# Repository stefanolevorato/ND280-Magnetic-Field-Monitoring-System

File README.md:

# I2C-TMAG Sensor Array

Project for ATmega328PB-based TMAG5273 magnetic sensor bring-up and future sensor array development.

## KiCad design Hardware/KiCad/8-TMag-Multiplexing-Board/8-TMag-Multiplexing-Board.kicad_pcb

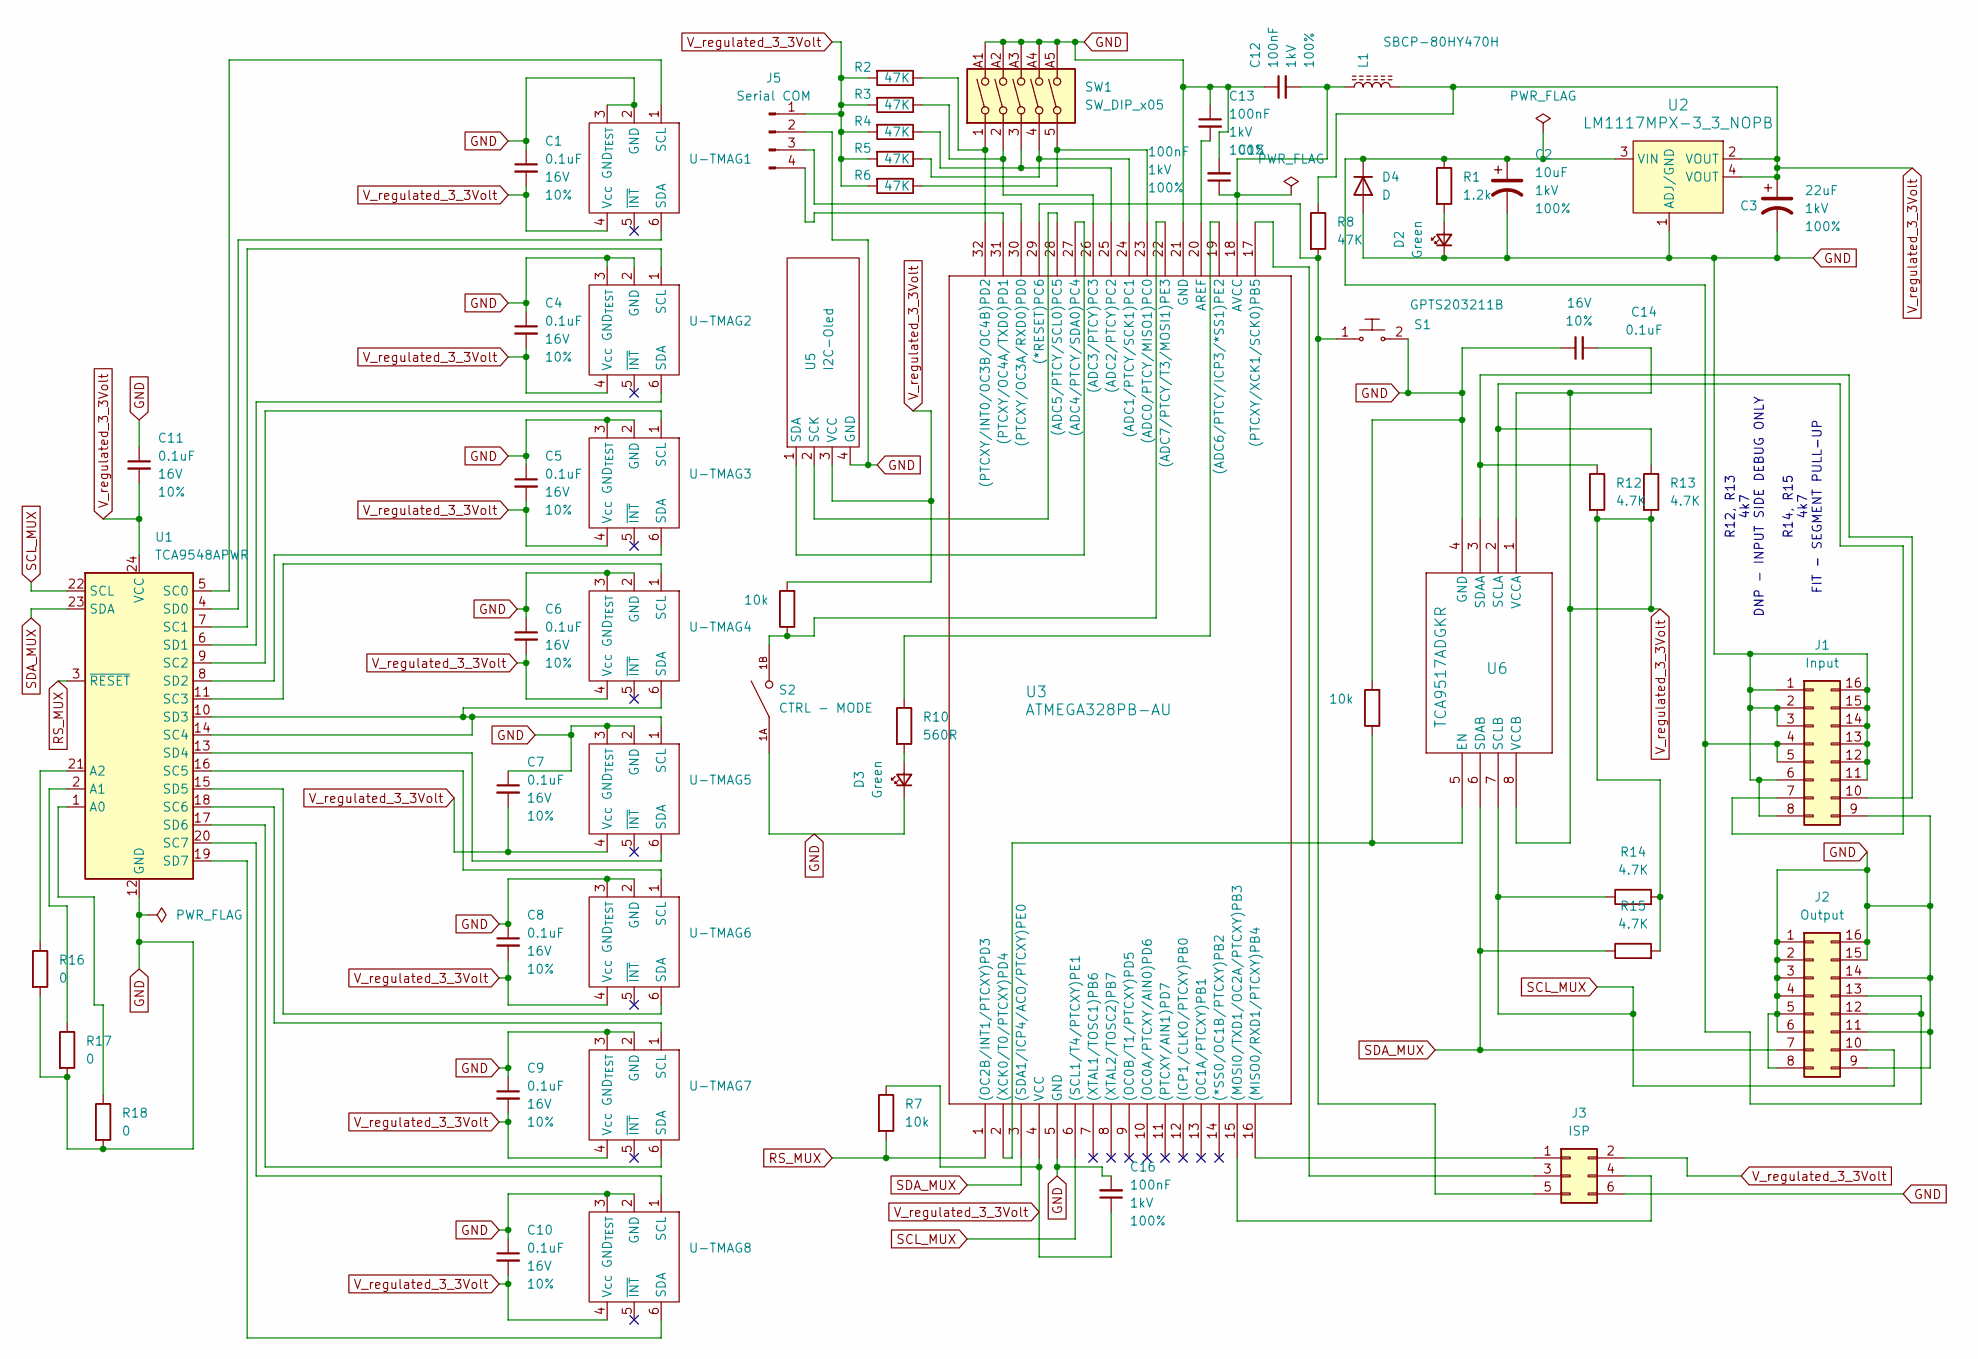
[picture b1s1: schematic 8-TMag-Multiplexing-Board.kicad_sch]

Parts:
C1, C4, C5, C6, C7, C8, C9, C10, C11, C14: 0.1uF; C_0402_1005Metric; Voltage 16V; Tolerance 10%
C2: 10uF; CP_Radial_D4.0mm_P2.00mm; Voltage 1kV; Tolerance 100%
C3: 22uF; CP_Radial_D4.0mm_P2.00mm; Voltage 1kV; Tolerance 100%
C12, C13, C15, C16: 100nF; C_0603_1608Metric; Voltage 1kV; Tolerance 100%
D2, D3: Green; LED_1206_Bottom_Green
D4: D; D_1206_3216Metric_Pad1.42x1.75mm_HandSolder
J1: Input; PinSocket_2x08_P2.54mm_Horizontal
J2: Output; PinSocket_2x08_P2.54mm_Horizontal
J3: ISP; PinHeader_2x03_P2.54mm_Vertical
J5: Serial COM; 1x04_P2.54mm
L1: SBCP-80HY470H; CP_Radial_D5.0mm_P2.50mm
R1: 1.2k; R_1206_3216Metric_Pad1.30x1.75mm_HandSolder
R2, R3, R4, R5, R6, R8: 47K; R_1206_3216Metric_Pad1.30x1.75mm_HandSolder
R7, R9, R11: 10k; R_1206_3216Metric_Pad1.30x1.75mm_HandSolder
R10: 560R; R_1206_3216Metric_Pad1.30x1.75mm_HandSolder
R12, R13, R14, R15: 4.7K; R_1206_3216Metric_Pad1.30x1.75mm_HandSolder
R16, R17, R18: 0; R_1206_3216Metric_Pad1.30x1.75mm_HandSolder
S1: GPTS203211B; PushButton_12x12mm_THT_GPTS203211B; MPN GPTS203211B; Digi-Key_PN CW181-ND
S2: CTRL - MODE; SW_DS01-254-L-01BE; PARTREV 1.0
SW1: SW_DIP_x05; 416131160805
U1: TCA9548APWR; TSSOP-24_4.4x7.8mm_P0.65mm
U2: LM1117MPX-3_3_NOPB; SOT-223; MPN LM1117MPX-3.3/NOPB; Digi-Key_PN LM1117MPX-3.3/NOPBCT-ND
U3: ATMEGA328PB-AU; 32A_MCH-M
U5: I2C-Oled; Oled128-32I2C
U6: TCA9517ADGKR; DGK8_TEX-L
U-TMAG1, U-TMAG2, U-TMAG3, U-TMAG4, U-TMAG5, U-TMAG6, U-TMAG7, U-TMAG8: TMAG5723-SOT23-I2C

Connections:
GND: C1.1, C2.2, C3.2, C4.1, C5.1, C6.1, C7.1, C8.1, C9.1, C10.1, C11.1, C12.1, C13.1, C14.1, C15.2, C16.2, D2.1 (K), D3.1 (K), D4.2 (A), J1.1, J1.2, J1.3, J1.6, J1.8, J1.9, J1.11, J1.12, J1.13, J1.14, J1.15, J1.16, J2.1, J2.2, J2.3, J2.4, J2.5, J2.6, J2.8, J2.9, J2.11, J2.14, J2.15, J2.16, J3.6, J5.2, R11.2, R16.2, R17.2, R18.2, S1.2, S2.1A, SW1.A1, SW1.A2, SW1.A3, SW1.A4, SW1.A5, U1.12 (GND), U2.1 (ADJ/GND), U3.5 (GND), U3.21 (GND), U5.4 (GND), U6.4 (GND), U-TMAG1.2 (GND), U-TMAG1.3 (GND_{TEST}), U-TMAG2.2 (GND), U-TMAG2.3 (GND_{TEST}), U-TMAG3.2 (GND), U-TMAG3.3 (GND_{TEST}), U-TMAG4.2 (GND), U-TMAG4.3 (GND_{TEST}), U-TMAG5.2 (GND), U-TMAG5.3 (GND_{TEST}), U-TMAG6.2 (GND), U-TMAG6.3 (GND_{TEST}), U-TMAG7.2 (GND), U-TMAG7.3 (GND_{TEST}), U-TMAG8.2 (GND), U-TMAG8.3 (GND_{TEST})
unnamed: D2.2 (A), R1.2
unnamed: D3.2 (A), R10.2
unnamed: C2.1, D4.1 (K), J1.4, J1.5, J2.12, J2.13, R1.1, U2.3 (VIN)
unnamed: J1.7, R13.1, U6.2 (SCLA)
unnamed: J1.10, R12.1, U6.3 (SDAA)
unnamed: J3.1, U3.16 ((MISO0/RXD1/PTCXY)PB4)
unnamed: J3.3, U3.17 ((PTCXY/XCK1/SCK0)PB5)
unnamed: J3.4, U3.15 ((MOSI0/TXD1/OC2A/PTCXY)PB3)
unnamed: J3.5, R8.2, S1.1, U3.29 ((*RESET)PC6)
unnamed: J5.3, U3.30 ((PTCXY/OC3A/RXD0)PD0)
unnamed: J5.4, U3.31 ((PTCXY/OC4A/TXD0)PD1)
unnamed: R18.1, U1.1 (A0)
unnamed: R17.1, U1.2 (A1)
unnamed: R16.1, U1.21 (A2)
unnamed: R6.1, SW1.5, U3.23 ((ADC0/PTCY/MISO1)PC0)
unnamed: R5.1, SW1.4, U3.24 ((ADC1/PTCY/SCK1)PC1)
unnamed: R4.1, SW1.3, U3.25 ((ADC2/PTCY)PC2)
unnamed: R3.1, SW1.2, U3.26 ((ADC3/PTCY)PC3)
unnamed: U3.27 ((ADC4/PTCY/SDA0)PC4), U5.1 (SDA)
unnamed: U3.28 ((ADC5/PTCY/SCL0)PC5), U5.2 (SCK)
unnamed: R10.1, U3.19 ((ADC6/PTCY/ICP3/*SS1)PE2)
unnamed: R9.1, S2.1B, U3.22 ((ADC7/PTCY/T3/MOSI1)PE3)
unnamed: R2.1, SW1.1, U3.32 ((PTCXY/INT0/OC3B/OC4B)PD2)
unnamed: R11.1, U3.2 ((XCK0/T0/PTCXY)PD4), U6.5 (EN)
unnamed: C13.2, U3.20 (AREF)
unnamed: C12.2, C15.1, L1.1, U3.18 (AVCC)
unnamed: U1.5 (SC0), U-TMAG1.1 (SCL)
unnamed: U1.4 (SD0), U-TMAG1.6 (SDA)
unnamed: U1.7 (SC1), U-TMAG2.1 (SCL)
unnamed: U1.6 (SD1), U-TMAG2.6 (SDA)
unnamed: U1.9 (SC2), U-TMAG3.1 (SCL)
unnamed: U1.8 (SD2), U-TMAG3.6 (SDA)
unnamed: U1.11 (SC3), U-TMAG4.1 (SCL)
unnamed: U1.10 (SD3), U1.14 (SC4), U-TMAG4.6 (SDA), U-TMAG5.1 (SCL)
unnamed: U1.13 (SD4), U-TMAG5.6 (SDA)
unnamed: U1.16 (SC5), U-TMAG6.1 (SCL)
unnamed: U1.15 (SD5), U-TMAG6.6 (SDA)
unnamed: U1.18 (SC6), U-TMAG7.1 (SCL)
unnamed: U1.17 (SD6), U-TMAG7.6 (SDA)
unnamed: U1.20 (SC7), U-TMAG8.1 (SCL)
unnamed: U1.19 (SD7), U-TMAG8.6 (SDA)
RS_MUX: R7.2, U1.3 (~RESET), U3.1 ((OC2B/INT1/PTCXY)PD3)
SCL_MUX: J2.10, R14.1, U1.22 (SCL), U3.6 ((SCL1/T4/PTCXY)PE1), U6.7 (SCLB)
SDA_MUX: J2.7, R15.1, U1.23 (SDA), U3.3 ((SDA1/ICP4/ACO/PTCXY)PE0), U6.6 (SDAB)
V_regulated_3_3Volt: C1.2, C3.1, C4.2, C5.2, C6.2, C7.2, C8.2, C9.2, C10.2, C11.2, C14.2, C16.1, J3.2, J5.1, L1.2, R2.2, R3.2, R4.2, R5.2, R6.2, R7.1, R8.1, R9.2, R12.2, R13.2, R14.2, R15.2, U1.24 (VCC), U2.2 (VOUT), U2.4 (VOUT), U3.4 (VCC), U5.3 (VCC), U6.1 (VCCA), U6.8 (VCCB), U-TMAG1.4 (Vcc), U-TMAG2.4 (Vcc), U-TMAG3.4 (Vcc), U-TMAG4.4 (Vcc), U-TMAG5.4 (Vcc), U-TMAG6.4 (Vcc), U-TMAG7.4 (Vcc), U-TMAG8.4 (Vcc)

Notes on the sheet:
R12, R13 4k7 DNP - INPUT SIDE DEBUG ONLY R14, R15 4k7 FIT - SEGMENT PULL-UP

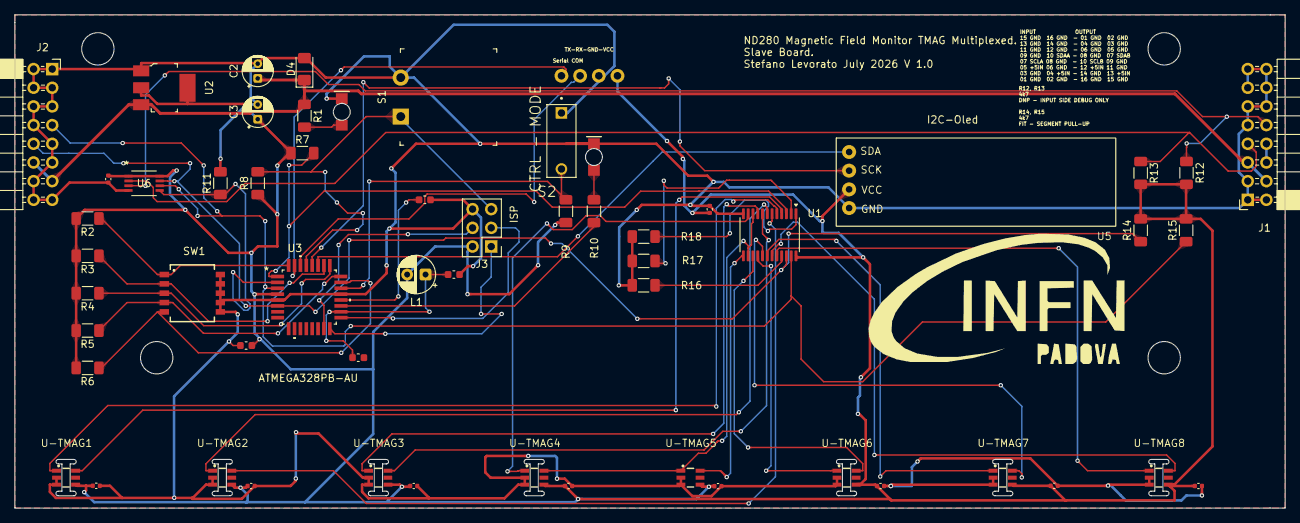
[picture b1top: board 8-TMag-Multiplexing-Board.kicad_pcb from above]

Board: 2 copper layers, 172.7 x 67.1 mm, 58 parts (0 on the bottom side), 46 nets.

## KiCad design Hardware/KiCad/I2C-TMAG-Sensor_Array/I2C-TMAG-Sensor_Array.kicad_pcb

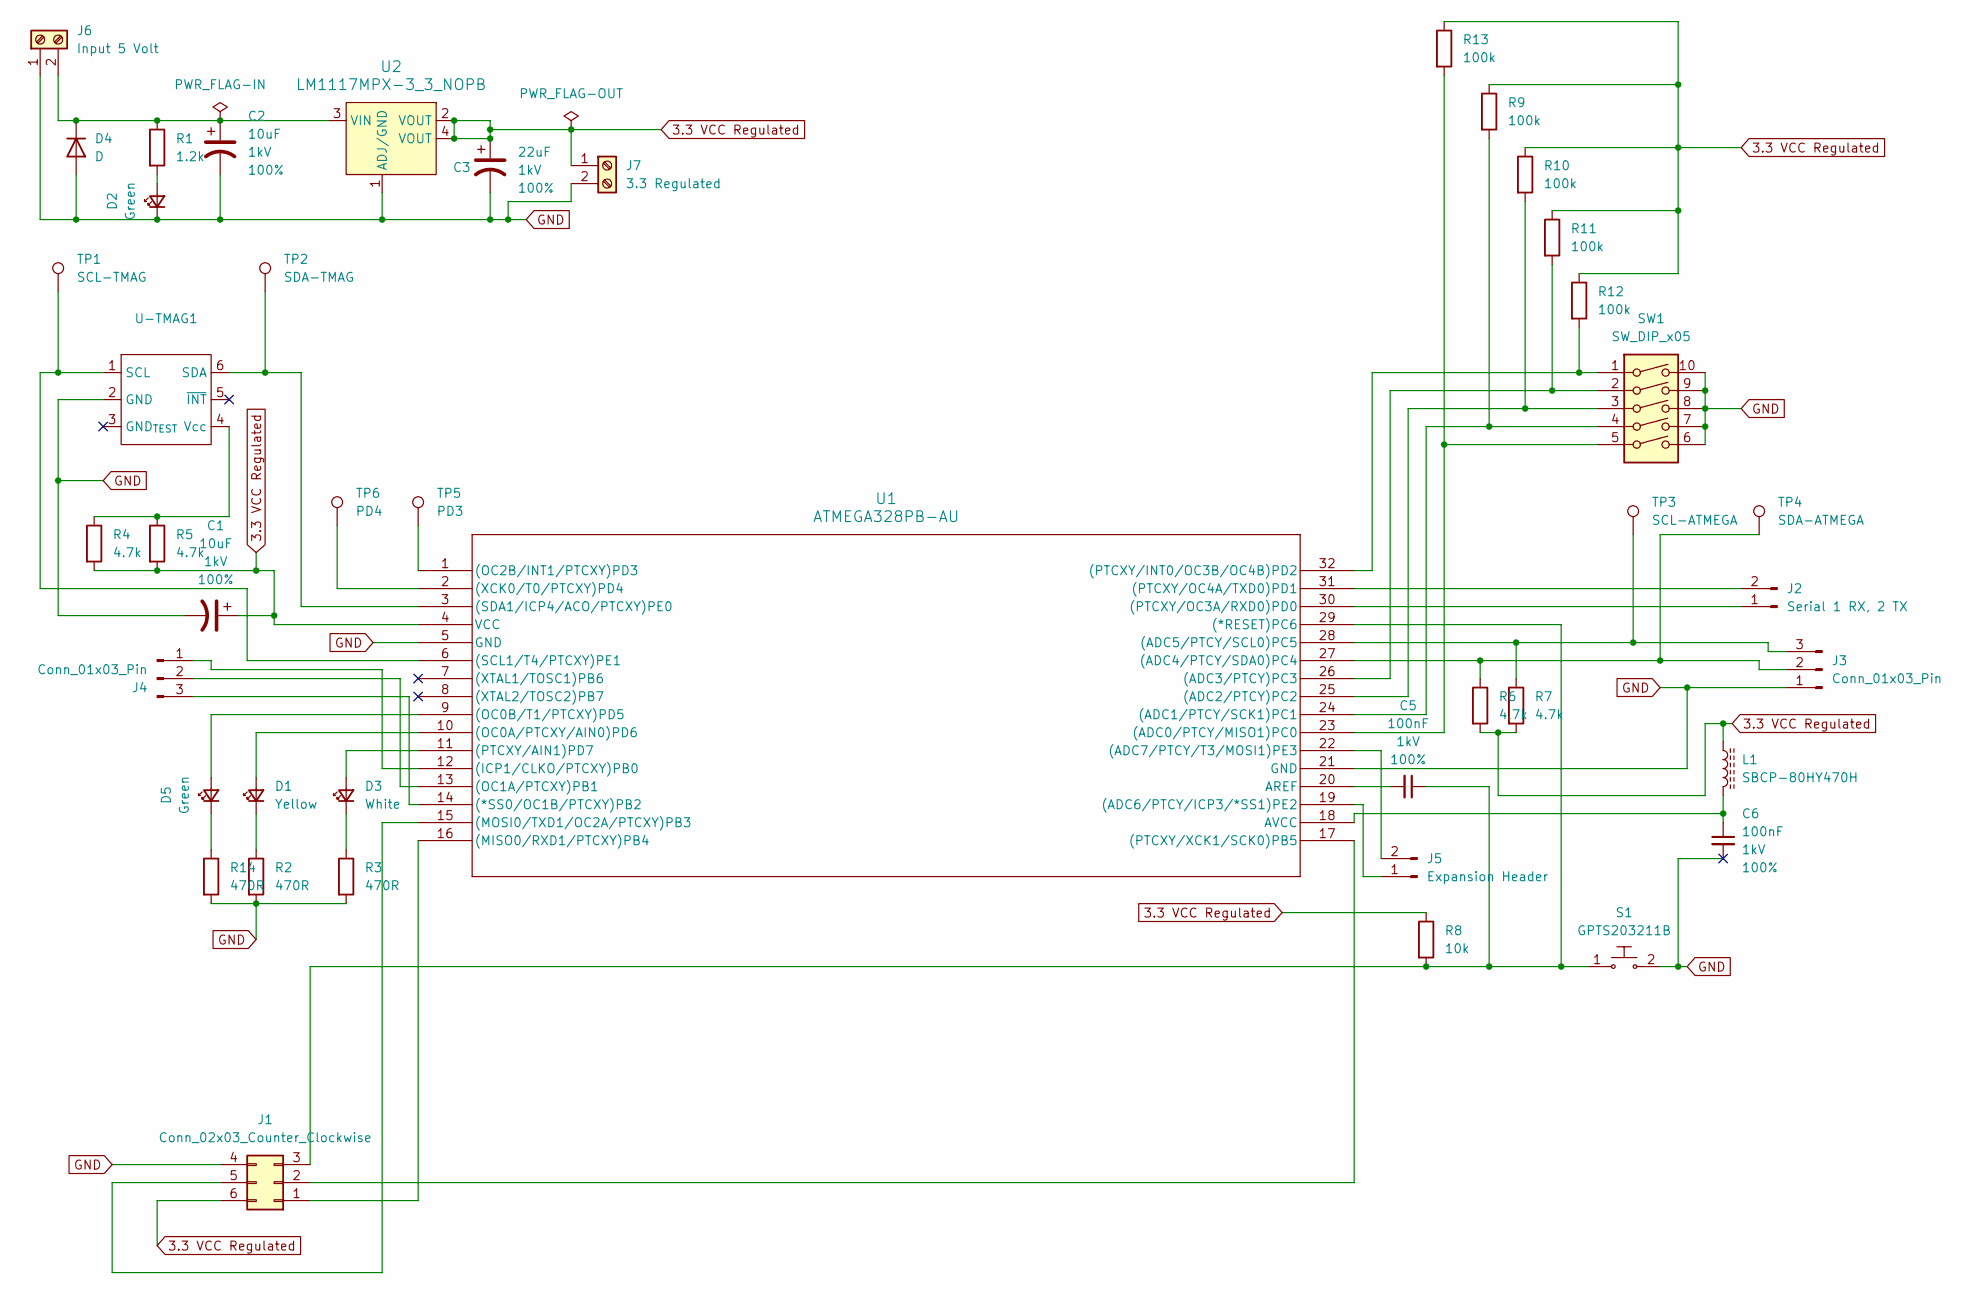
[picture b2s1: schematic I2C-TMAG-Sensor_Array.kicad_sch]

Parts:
C1, C2: 10uF; CP_Radial_D4.0mm_P2.00mm; Voltage 1kV; Tolerance 100%
C3: 22uF; CP_Radial_D4.0mm_P2.00mm; Voltage 1kV; Tolerance 100%
C5, C6: 100nF; C_0603_1608Metric; Voltage 1kV; Tolerance 100%
D1: Yellow; LED_1206_3216Metric_Yellow
D2, D5: Green; LED_1206_Bottom_Green
D3: White; LED_1206_3216Metric_White
D4: D; D_1206_3216Metric_Pad1.42x1.75mm_HandSolder
J1: Conn_02x03_Counter_Clockwise; SAMTEC_TSM-103-01-L-DV
J2: Serial 1 RX, 2 TX; TerminalBlock_Phoenix_MPT-0,5-2-2.54_1x02_P2.54mm_Horizontal
J3, J4: Conn_01x03_Pin; TerminalBlock_Phoenix_MPT-0,5-3-2.54_1x03_P2.54mm_Horizontal
J5: Expansion Header; TerminalBlock_Phoenix_MPT-0,5-2-2.54_1x02_P2.54mm_Horizontal
J6: Input 5 Volt; TerminalBlock_Phoenix_MPT-0,5-2-2.54_1x02_P2.54mm_Horizontal
J7: 3.3 Regulated; TerminalBlock_Phoenix_MPT-0,5-2-2.54_1x02_P2.54mm_Horizontal
L1: SBCP-80HY470H; CP_Radial_D5.0mm_P2.50mm
R1: 1.2k; R_1206_3216Metric_Pad1.30x1.75mm_HandSolder
R2, R3, R14: 470R; R_1206_3216Metric_Pad1.30x1.75mm_HandSolder
R4, R5, R6, R7: 4.7k; R_1206_3216Metric_Pad1.30x1.75mm_HandSolder
R8: 10k; R_1206_3216Metric_Pad1.30x1.75mm_HandSolder
R9, R10, R11, R12, R13: 100k; R_1206_3216Metric_Pad1.30x1.75mm_HandSolder
S1: GPTS203211B; PushButton_12x12mm_THT_GPTS203211B; MPN GPTS203211B; Digi-Key_PN CW181-ND
SW1: SW_DIP_x05; DIP-5vie
TP1: SCL-TMAG; TestPoint_Pad_D2.0mm
TP2: SDA-TMAG; TestPoint_Pad_D2.0mm
TP3: SCL-ATMEGA; TestPoint_Pad_D2.0mm
TP4: SDA-ATMEGA; TestPoint_Pad_D2.0mm
TP5: PD3; TestPoint_Pad_D2.0mm
TP6: PD4; TestPoint_Pad_D2.0mm
U1: ATMEGA328PB-AU; 32A_MCH
U2: LM1117MPX-3_3_NOPB; SOT-223; MPN LM1117MPX-3.3/NOPB; Digi-Key_PN LM1117MPX-3.3/NOPBCT-ND
U-TMAG1: TNAG5723-SOT23-I2C

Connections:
3.3 VCC Regulated: C1.1, C3.1, J1.6, J7.1, L1.1, R4.2, R5.2, R6.2, R7.2, R8.1, R9.1, R10.1, R11.1, R12.1, R13.1, U1.4 (VCC), U2.2 (VOUT), U2.4 (VOUT)
GND: C1.2, C2.2, C3.2, C6.2, D2.1 (K), D4.2 (A), J1.4, J3.1, J6.1, J7.2, R2.2, R3.2, R14.2, S1.2, SW1.6, SW1.7, SW1.8, SW1.9, SW1.10, U1.5 (GND), U1.21 (GND), U2.1 (ADJ/GND), U-TMAG1.2 (GND)
unnamed: D1.2 (A), U1.10 ((OC0A/PTCXY/AIN0)PD6)
unnamed: D1.1 (K), R2.1
unnamed: D2.2 (A), R1.2
unnamed: D3.2 (A), U1.11 ((PTCXY/AIN1)PD7)
unnamed: D3.1 (K), R3.1
unnamed: C2.1, D4.1 (K), J6.2, R1.1, U2.3 (VIN)
unnamed: D5.2 (A), U1.9 ((OC0B/T1/PTCXY)PD5)
unnamed: D5.1 (K), R14.1
unnamed: J1.1, U1.16 ((MISO0/RXD1/PTCXY)PB4)
unnamed: J1.2, U1.17 ((PTCXY/XCK1/SCK0)PB5)
unnamed: C5.1, J1.3, R8.2, S1.1, U1.29 ((*RESET)PC6)
unnamed: J1.5, U1.15 ((MOSI0/TXD1/OC2A/PTCXY)PB3)
unnamed: J2.1, U1.30 ((PTCXY/OC3A/RXD0)PD0)
unnamed: J2.2, U1.31 ((PTCXY/OC4A/TXD0)PD1)
unnamed: J3.2, R6.1, TP4.1, U1.27 ((ADC4/PTCY/SDA0)PC4)
unnamed: J3.3, R7.1, TP3.1, U1.28 ((ADC5/PTCY/SCL0)PC5)
unnamed: J4.1, U1.12 ((ICP1/CLKO/PTCXY)PB0)
unnamed: J4.2, U1.13 ((OC1A/PTCXY)PB1)
unnamed: J4.3, U1.14 ((*SS0/OC1B/PTCXY)PB2)
unnamed: J5.1, U1.19 ((ADC6/PTCY/ICP3/*SS1)PE2)
unnamed: J5.2, U1.22 ((ADC7/PTCY/T3/MOSI1)PE3)
unnamed: R13.2, SW1.5, U1.23 ((ADC0/PTCY/MISO1)PC0)
unnamed: R9.2, SW1.4, U1.24 ((ADC1/PTCY/SCK1)PC1)
unnamed: R10.2, SW1.3, U1.25 ((ADC2/PTCY)PC2)
unnamed: R11.2, SW1.2, U1.26 ((ADC3/PTCY)PC3)
unnamed: TP5.1, U1.1 ((OC2B/INT1/PTCXY)PD3)
unnamed: R12.2, SW1.1, U1.32 ((PTCXY/INT0/OC3B/OC4B)PD2)
unnamed: TP6.1, U1.2 ((XCK0/T0/PTCXY)PD4)
unnamed: C5.2, U1.20 (AREF)
unnamed: C6.1, L1.2, U1.18 (AVCC)
unnamed: TP1.1, U1.6 ((SCL1/T4/PTCXY)PE1), U-TMAG1.1 (SCL)
unnamed: TP2.1, U1.3 ((SDA1/ICP4/ACO/PTCXY)PE0), U-TMAG1.6 (SDA)
unnamed: R4.1, R5.1, U-TMAG1.4 (Vcc)

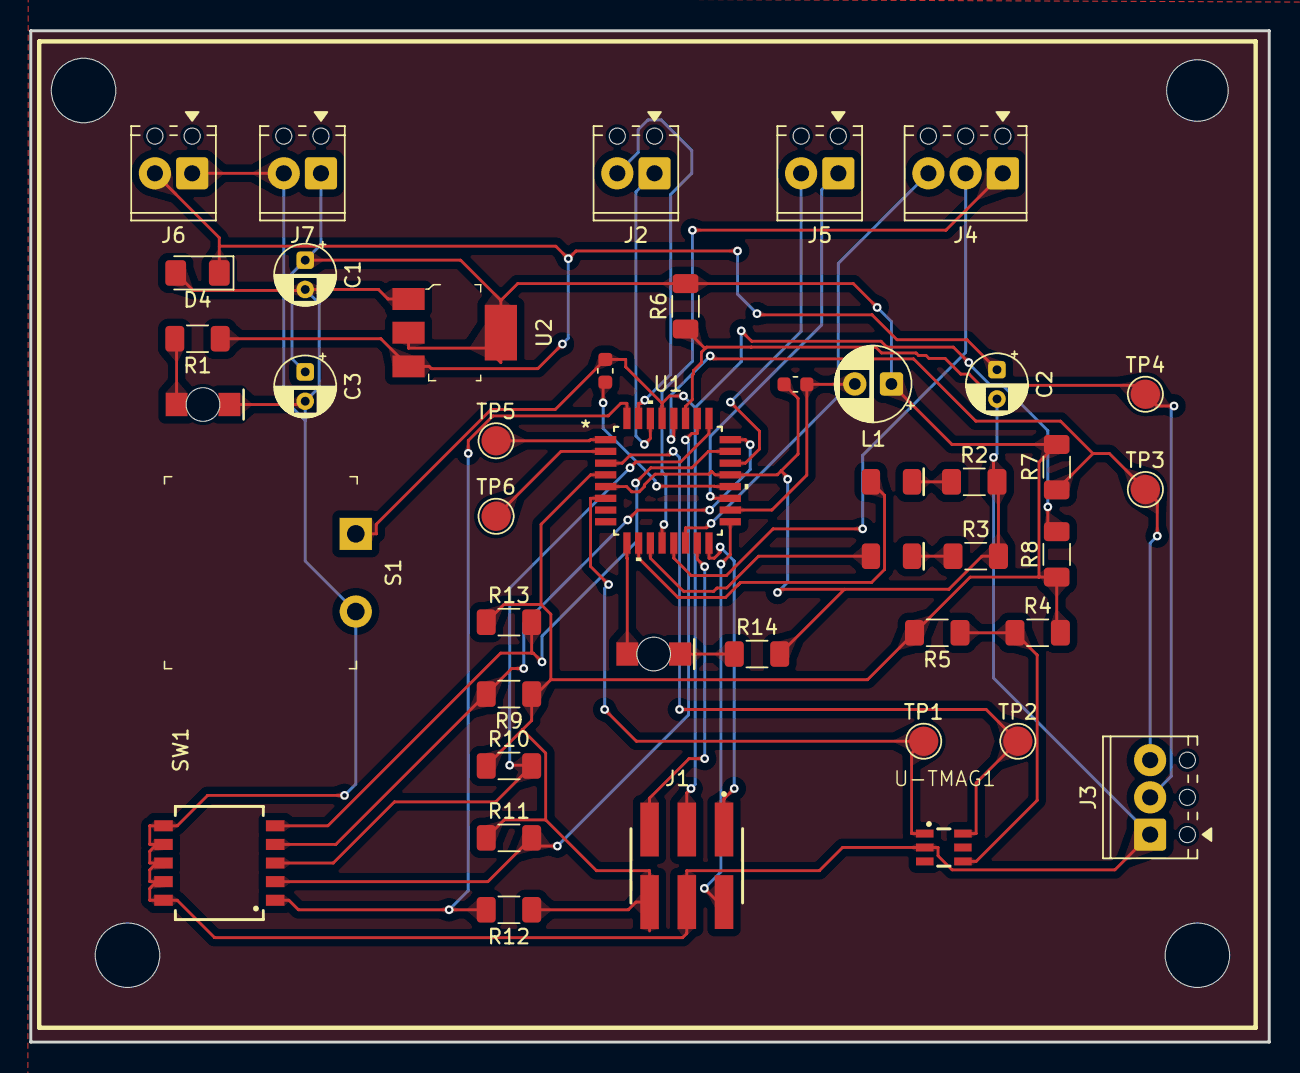
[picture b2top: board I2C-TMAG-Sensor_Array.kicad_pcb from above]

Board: 2 copper layers, 84.5 x 69.0 mm, 43 parts (0 on the bottom side), 35 nets.

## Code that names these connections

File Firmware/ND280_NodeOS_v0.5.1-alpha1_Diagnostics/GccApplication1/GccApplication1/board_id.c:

#include <avr/io.h>
#include <stdint.h>
#include "board_id.h"

void board_id_init(void)
{
    /* bit0..bit3 = PC0..PC3; bit4 = PD2. External 100 kohm pull-ups. */
    DDRC &= ~((1 << PC0) | (1 << PC1) | (1 << PC2) | (1 << PC3));
    DDRD &= ~(1 << PD2);

    PORTC &= ~((1 << PC0) | (1 << PC1) | (1 << PC2) | (1 << PC3));
    PORTD &= ~(1 << PD2);
}

uint8_t board_id_read(void)
{
    uint8_t raw = 0;

    if (PINC & (1 << PC0)) raw |= (1 << 0);
    if (PINC & (1 << PC1)) raw |= (1 << 1);
    if (PINC & (1 << PC2)) raw |= (1 << 2);
    if (PINC & (1 << PC3)) raw |= (1 << 3);
    if (PIND & (1 << PD2)) raw |= (1 << 4);

    /* Switch ON pulls low, so invert to obtain the board number. */
    return (uint8_t)((~raw) & 0x1FU);
}

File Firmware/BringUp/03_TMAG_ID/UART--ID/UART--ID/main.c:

#define F_CPU 1000000UL

#include <avr/io.h>
#include <util/delay.h>
#include <stdint.h>

#include "uart0.h"
#include "twi1.h"

#define TMAG5273_ADDR       0x35
#define TMAG5273_DEVICE_ID  0x0D

int main(void)
{
    uint8_t id = 0;

    uart0_init();
    twi1_init();

    DDRD |= (1 << PD5) | (1 << PD6) | (1 << PD7);

    uart0_print("\r\n=================================\r\n");
    uart0_print("BU005 - TMAG5273 DEVICE_ID Read\r\n");
    uart0_print("=================================\r\n");
    uart0_print("UART0: 4800 baud\r\n");
    uart0_print("TWI1 : PE0=SDA1, PE1=SCL1\r\n");
    uart0_print("Device address: 0x35\r\n\r\n");

    while (1)
    {
        uart0_print("Reading DEVICE_ID register 0x0D...\r\n");

        if (twi1_read_register(TMAG5273_ADDR, TMAG5273_DEVICE_ID, &id))
        {
            uart0_print("DEVICE_ID = 0x");
            uart0_print_hex8(id);
            uart0_print("\r\nPASS\r\n\r\n");
            PORTD ^= (1 << PD7);
        }
        else
        {
            uart0_print("Read failed, TWI status = 0x");
            uart0_print_hex8(twi1_last_status());
            uart0_print("\r\nFAIL\r\n\r\n");
            PORTD ^= (1 << PD5);
        }

        _delay_ms(2000);
    }
}
